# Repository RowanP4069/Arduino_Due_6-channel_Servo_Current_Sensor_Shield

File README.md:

# Arduino_Due_6-channel_Servo_Current_Sensor_Shield

Project information - https://www.hackster.io/rpatterson/arduino-due-6-channel-servo-current-sensor-shield-6fad15

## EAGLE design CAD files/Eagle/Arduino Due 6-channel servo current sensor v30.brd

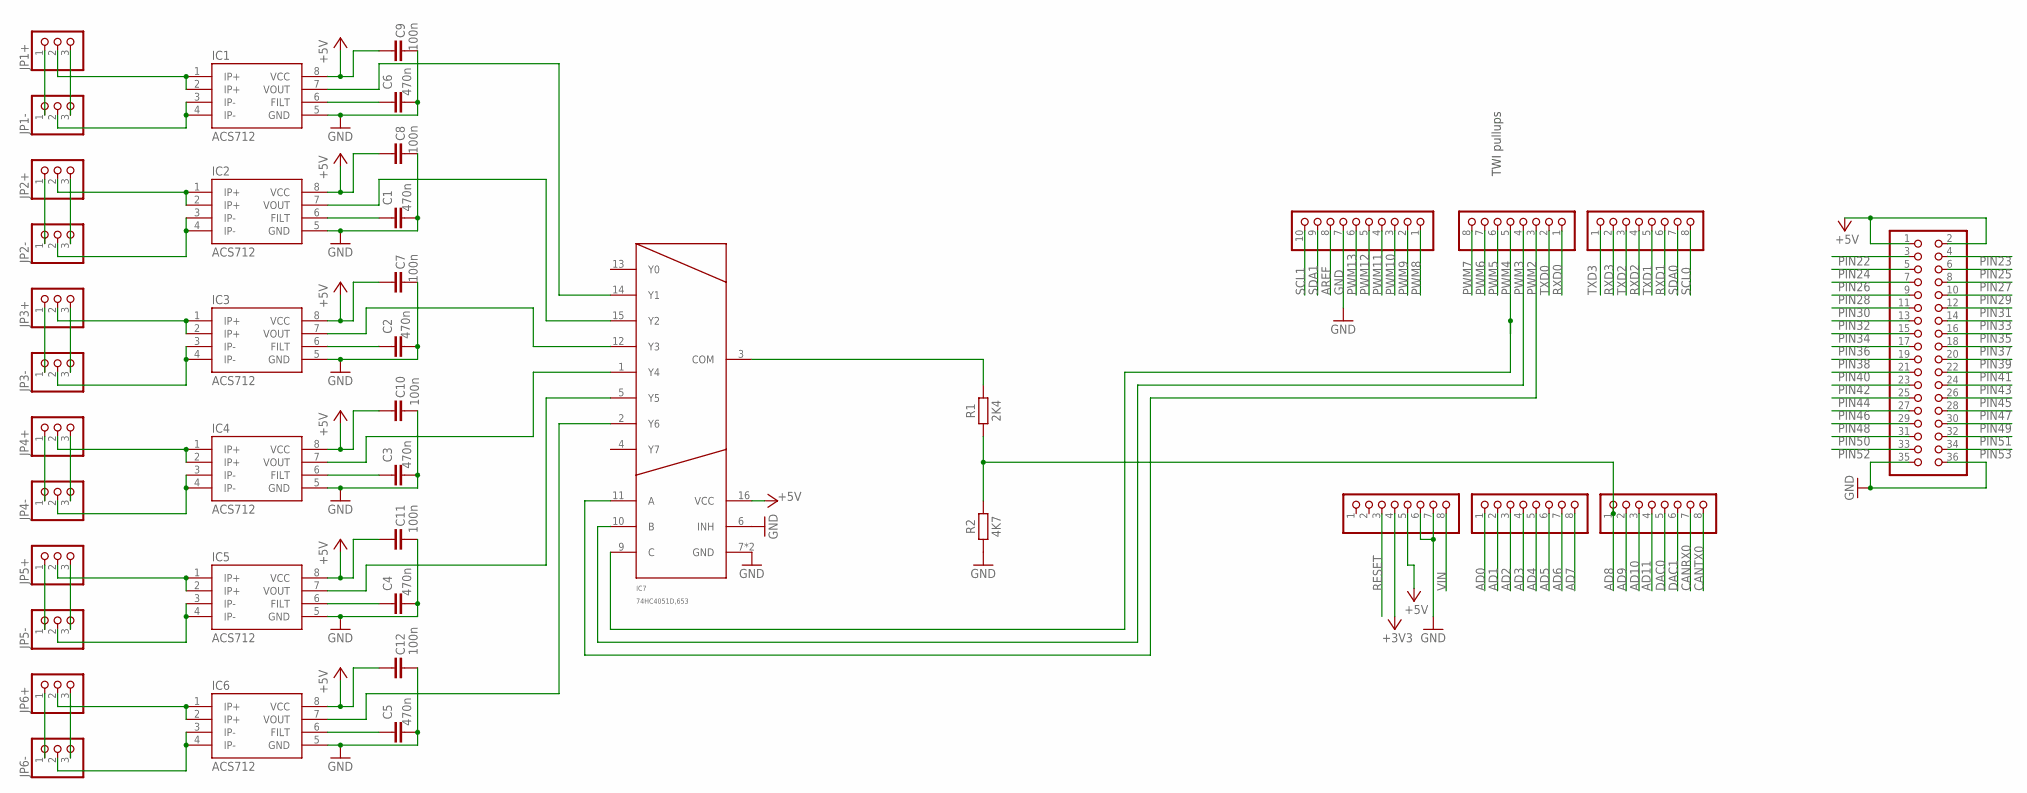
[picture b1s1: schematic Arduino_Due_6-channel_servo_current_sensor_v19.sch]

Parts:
ADCH: FH254-108DF08500V; 1X08
ADCL: FH254-108DF08500V; 1X08
C1, C2, C3, C4, C5, C6: 470n; CAPC3216X135
C7, C8, C9, C10, C11, C12: 100n; CAPC3216X135
COMMUNICATION: FH254-108DF08500V; 1X08
IC1, IC2, IC3, IC4, IC5, IC6: ACS712; SO08
IC7: 74HC4051D,653; SO16
JP1+, JP1-, JP2+, JP2-, JP3+, JP3-, JP4+, JP4-, JP5+, JP5-, JP6+, JP6-: PINHD-1X3; 1X03
POWER: FH254-108DF08500V; 1X08
PWMH: FH254-110DF08500V; 1X10
PWML: FH254-108DF08500V; 1X08
R1: 2K4; RESC3216X70
R2: 4K7; RESC3216X70
XIO: 18x2F-H8.5; 2X18

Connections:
1IP+: IC1.1 (IP+), IC1.2 (IP+), JP1+.2
1IP-: IC1.3 (IP-), IC1.4 (IP-), JP1-.2
2IP+: IC2.1 (IP+), IC2.2 (IP+), JP2+.2
2IP-: IC2.3 (IP-), IC2.4 (IP-), JP2-.2
3IP+: IC3.1 (IP+), IC3.2 (IP+), JP3+.2
3IP-: IC3.3 (IP-), IC3.4 (IP-), JP3-.2
4IP+: IC4.1 (IP+), IC4.2 (IP+), JP4+.2
4IP-: IC4.3 (IP-), IC4.4 (IP-), JP4-.2
5IP+: IC5.1 (IP+), IC5.2 (IP+), JP5+.2
5IP-: IC5.3 (IP-), IC5.4 (IP-), JP5-.2
6IP+: IC6.1 (IP+), IC6.2 (IP+), JP6+.2
6IP-: IC6.3 (IP-), IC6.4 (IP-), JP6-.2
+3V3: POWER.4
+5V: C7.1, C8.1, C9.1, C10.1, C11.1, C12.1, IC1.8 (VCC), IC2.8 (VCC), IC3.8 (VCC), IC4.8 (VCC), IC5.8 (VCC), IC6.8 (VCC), IC7.16 (VCC), POWER.5, XIO.1, XIO.2
AD0: ADCL.1
AD1: ADCL.2
AD2: ADCL.3
AD3: ADCL.4
AD4: ADCL.5
AD5: ADCL.6
AD6: ADCL.7
AD7: ADCL.8
AD8: ADCH.1, R1.1, R2.2
AD9: ADCH.2
AD10: ADCH.3
AD11: ADCH.4
AREF: PWMH.8
CANRX0: ADCH.7
CANTX0: ADCH.8
DAC0: ADCH.5
DAC1: ADCH.6
FILTER1: C6.1, IC1.6 (FILT)
FILTER2: C1.1, IC2.6 (FILT)
FILTER3: C2.1, IC3.6 (FILT)
FILTER4: C3.1, IC4.6 (FILT)
FILTER5: C4.1, IC5.6 (FILT)
FILTER6: C5.1, IC6.6 (FILT)
GND: C1.2, C2.2, C3.2, C4.2, C5.2, C6.2, C7.2, C8.2, C9.2, C10.2, C11.2, C12.2, IC1.5 (GND), IC2.5 (GND), IC3.5 (GND), IC4.5 (GND), IC5.5 (GND), IC6.5 (GND), IC7.6 (INH), IC7.7 (GND), IC7.8 (GND), POWER.6, POWER.7, PWMH.7, R2.1, XIO.35, XIO.36
unnamed: JP6+.1, JP6-.1
unnamed: JP6+.3, JP6-.3
unnamed: JP5+.1, JP5-.1
unnamed: JP5+.3, JP5-.3
unnamed: JP4+.1, JP4-.1
unnamed: JP4+.3, JP4-.3
unnamed: JP3+.1, JP3-.1
unnamed: JP3+.3, JP3-.3
unnamed: JP2+.1, JP2-.1
unnamed: JP2+.3, JP2-.3
unnamed: JP1+.1, JP1-.1
unnamed: JP1+.3, JP1-.3
PIN22: XIO.3
PIN23: XIO.4
PIN24: XIO.5
PIN25: XIO.6
PIN26: XIO.7
PIN27: XIO.8
PIN28: XIO.9
PIN29: XIO.10
PIN30: XIO.11
PIN31: XIO.12
PIN32: XIO.13
PIN33: XIO.14
PIN34: XIO.15
PIN35: XIO.16
PIN36: XIO.17
PIN37: XIO.18
PIN38: XIO.19
PIN39: XIO.20
PIN40: XIO.21
PIN41: XIO.22
PIN42: XIO.23
PIN43: XIO.24
PIN44: XIO.25
PIN45: XIO.26
PIN46: XIO.27
PIN47: XIO.28
PIN48: XIO.29
PIN49: XIO.30
PIN50: XIO.31
PIN51: XIO.32
PIN52: XIO.33
PIN53: XIO.34
PWM2: IC7.11 (A), PWML.3
PWM3: IC7.10 (B), PWML.4
PWM4: IC7.9 (C), PWML.5
PWM5: PWML.6
PWM6: PWML.7
PWM7: PWML.8
PWM8: PWMH.1
PWM9: PWMH.2
PWM10: PWMH.3
PWM11: PWMH.4
PWM12: PWMH.5
PWM13: PWMH.6
RESET: POWER.3
RXD0: PWML.1
RXD1: COMMUNICATION.6
RXD2: COMMUNICATION.4
RXD3: COMMUNICATION.2
SCL0: COMMUNICATION.8
SCL1: PWMH.10
SDA0: COMMUNICATION.7
SDA1: PWMH.9
TXD0: PWML.2
TXD1: COMMUNICATION.5
TXD2: COMMUNICATION.3
TXD3: COMMUNICATION.1
VIN: POWER.8
VIOUT1: IC1.7 (VOUT), IC7.14 (Y1)
VIOUT2: IC2.7 (VOUT), IC7.15 (Y2)
VIOUT3: IC3.7 (VOUT), IC7.12 (Y3)
VIOUT4: IC4.7 (VOUT), IC7.1 (Y4)
VIOUT5: IC5.7 (VOUT), IC7.5 (Y5)
VIOUT6: IC6.7 (VOUT), IC7.2 (Y6)
Z-COMMON: IC7.3 (COM), R1.2

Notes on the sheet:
TWI pullups

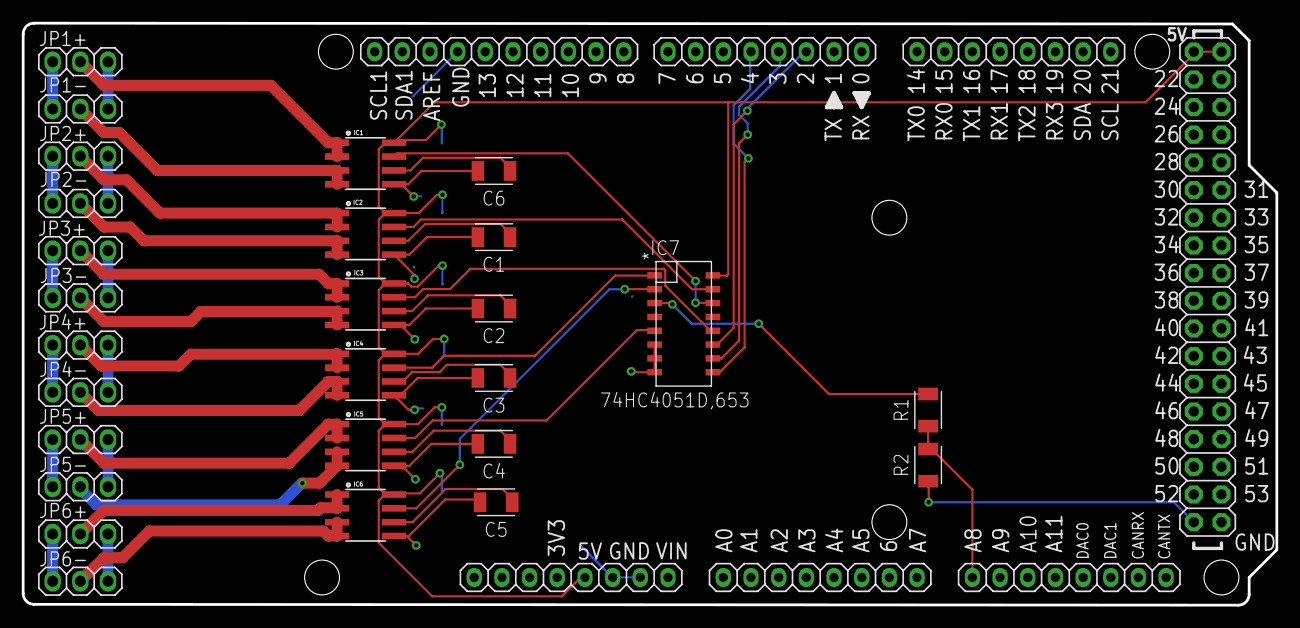
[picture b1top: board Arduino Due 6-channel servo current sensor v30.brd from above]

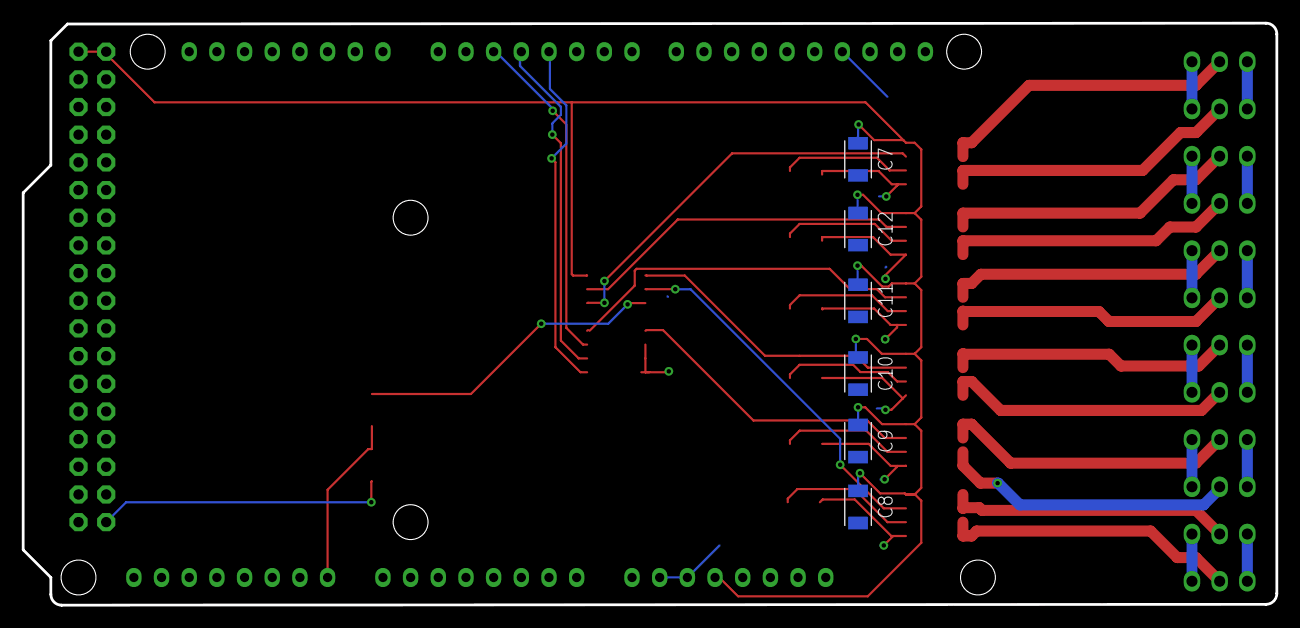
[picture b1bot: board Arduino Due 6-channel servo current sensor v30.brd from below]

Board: 2 copper layers, 115.1 x 53.4 mm, 40 parts (6 on the bottom side), 43 nets.
